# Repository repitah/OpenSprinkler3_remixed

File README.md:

# OpenSprinkler3_remixed
Custom board based off OpenSprinkler 3 using ESP12 ESP8266 board.
The mainboard is split from the driver board allowing a separation of parts and was cheaper for me to implement a smaller system. 

Design uses EagleCAD

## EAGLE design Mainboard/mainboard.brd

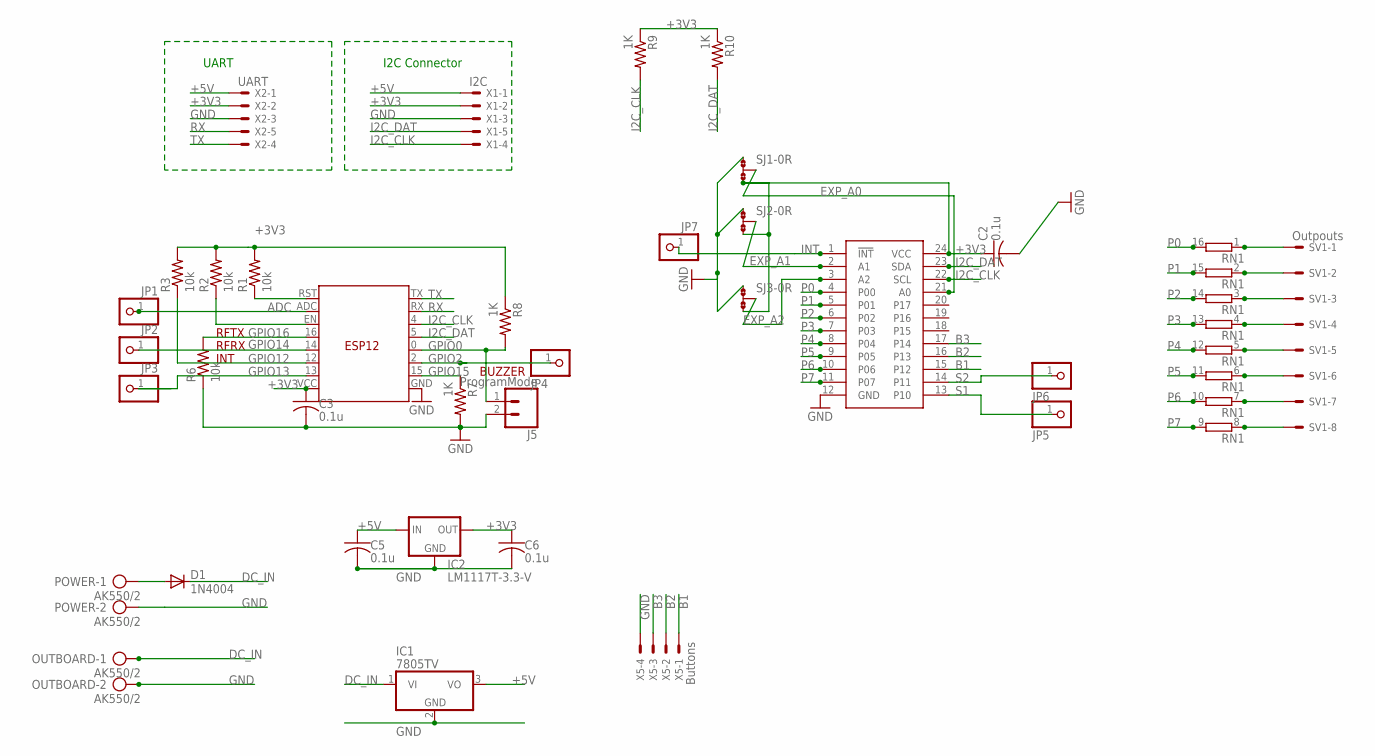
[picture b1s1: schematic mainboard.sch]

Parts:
C2, C3, C5, C6: 0.1u; C050-045X075
D1: 1N4004; DO41-10
ESP: ESP-12N; ESP12_WES
IC1: 7805TV; TO220V
IC2: LM1117T-3.3-V; TO220V
J5: ProgramMode; 1X02
JP1, JP2, JP3, JP4, JP5, JP6, JP7: PINHD-1X1; 1X01
OUTBOARD: AK550/2
PCA9555: PCA9555; TSSOP24
POWER: AK550/2
R1, R3, R6: 10k; 0204/7
R2: 10k; 0204/5
R7, R8, R9, R10: 1K; 0204/7
RN1: 8R-P; DIL16
SJ1, SJ2, SJ3: 0R-JUMPA; A0R-JMP
SV1: Outpouts; 22-23-2081
X1: I2C; 22-23-2051
X2: UART; 22-23-2051
X5: Buttons; 22-23-2041

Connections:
+3V3: C2.1, C3.1, C6.1, ESP.VCC, IC2.2 (OUT), PCA9555.24 (VCC), R1.2, R2.2, R3.2, R8.1, R9.1, R10.1, SJ1.3, SJ2.3, SJ3.3, X1.2, X2.2
+5V: C5.1, IC1.3 (VO), IC2.3 (IN), X1.1, X2.1
ADC: ESP.ADC, JP1.1
B1: PCA9555.15 (P12), X5.1
B2: PCA9555.16 (P13), X5.2
B3: PCA9555.17 (P14), X5.3
DC_IN: D1.C, IC1.1 (VI), OUTBOARD.1
EXP_A0: PCA9555.21 (A0), SJ1.2
EXP_A1: PCA9555.2 (A1), SJ2.2
EXP_A2: PCA9555.3 (A2), SJ3.2
GND: C2.2, C3.2, C5.2, C6.2, ESP.GND, IC1.2 (GND), IC2.1 (GND), J5.2, OUTBOARD.2, PCA9555.12 (GND), POWER.2, R6.1, R7.2, SJ1.1, SJ2.1, SJ3.1, X1.3, X2.3, X5.4
GPIO0: ESP.0 (G0), J5.1, R8.2
GPIO2: ESP.2 (G2), JP4.1
GPIO12: ESP.12 (G12), R3.1
GPIO13: ESP.13 (G13), JP3.1
GPIO14: ESP.14 (G14), JP2.1
GPIO15: ESP.15 (G15), R7.1
GPIO16: ESP.16 (G16), R6.2
I2C_CLK: ESP.4 (G4), PCA9555.22 (SCL), R9.2, X1.4
I2C_DAT: ESP.5 (G5), PCA9555.23 (SDA), R10.2, X1.5
INT: JP7.1, PCA9555.1 (!INT)
unnamed: D1.A, POWER.1
unnamed: ESP.EN, R2.1
unnamed: RN1.1, SV1.1
unnamed: RN1.2 (1), SV1.2
unnamed: RN1.3 (1), SV1.3
unnamed: RN1.4 (1), SV1.4
unnamed: RN1.5 (1), SV1.5
unnamed: RN1.6 (1), SV1.6
unnamed: RN1.7 (1), SV1.7
unnamed: RN1.8 (1), SV1.8
unnamed: ESP.RST, R1.1
P0: PCA9555.4 (P00), RN1.16 (2)
P1: PCA9555.5 (P01), RN1.15 (2)
P2: PCA9555.6 (P02), RN1.14 (2)
P3: PCA9555.7 (P03), RN1.13 (2)
P4: PCA9555.8 (P04), RN1.12 (2)
P5: PCA9555.9 (P05), RN1.11 (2)
P6: PCA9555.10 (P06), RN1.10 (2)
P7: PCA9555.11 (P07), RN1.9 (2)
RX: ESP.RX, X2.5
S1: JP5.1, PCA9555.13 (P10)
S2: JP6.1, PCA9555.14 (P11)
TX: ESP.TX, X2.4

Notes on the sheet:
I2C Connector
UART
RFRX
BUZZER
RFTX
INT

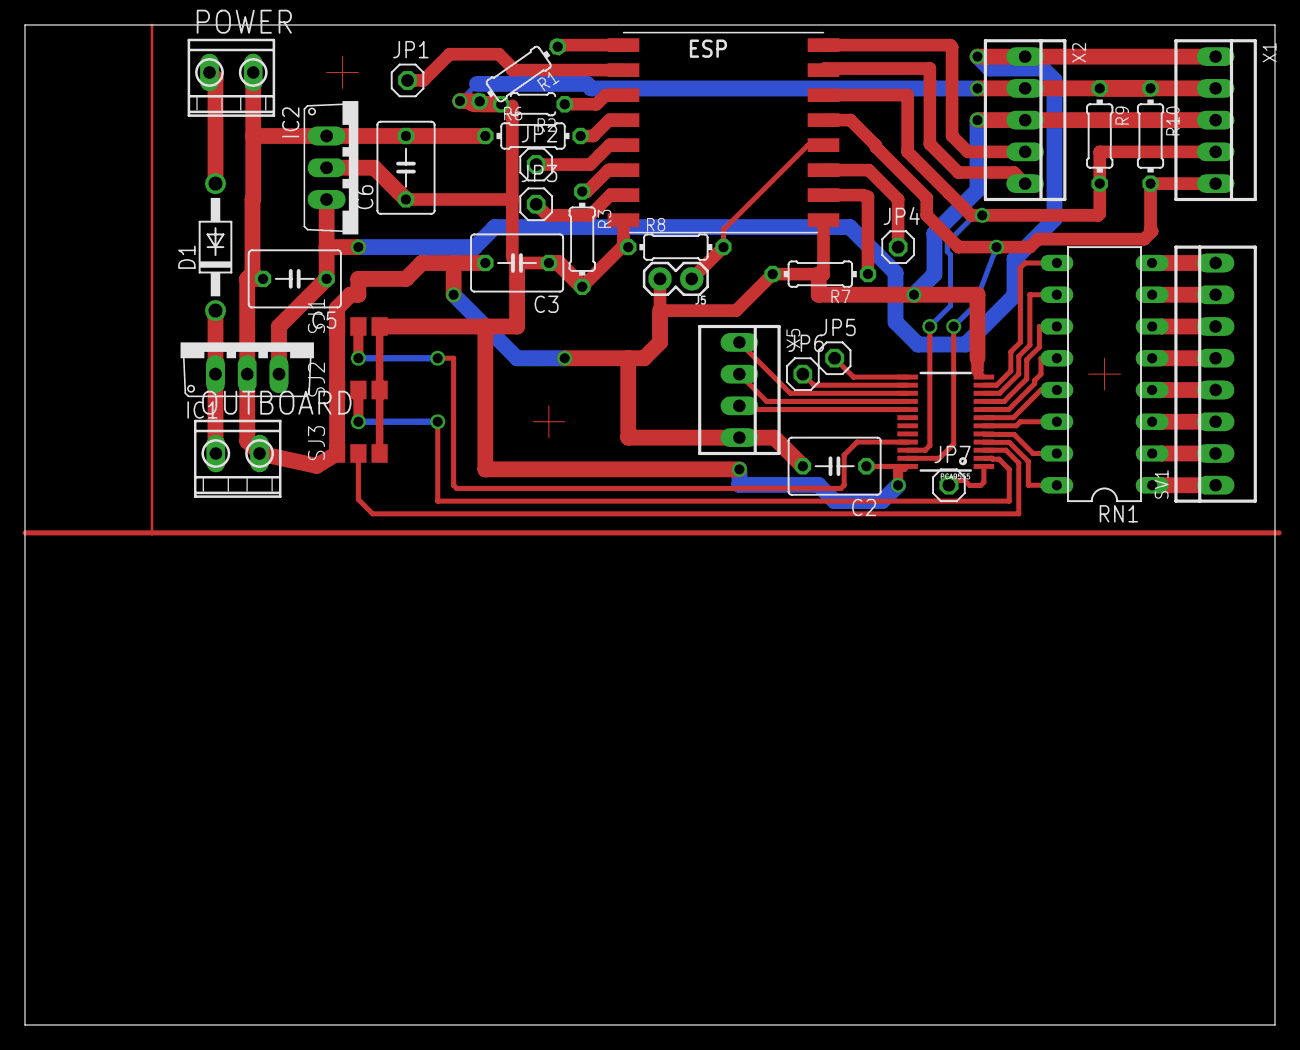
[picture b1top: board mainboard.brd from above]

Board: 2 copper layers, 100.0 x 80.0 mm, 35 parts (0 on the bottom side), 44 nets.

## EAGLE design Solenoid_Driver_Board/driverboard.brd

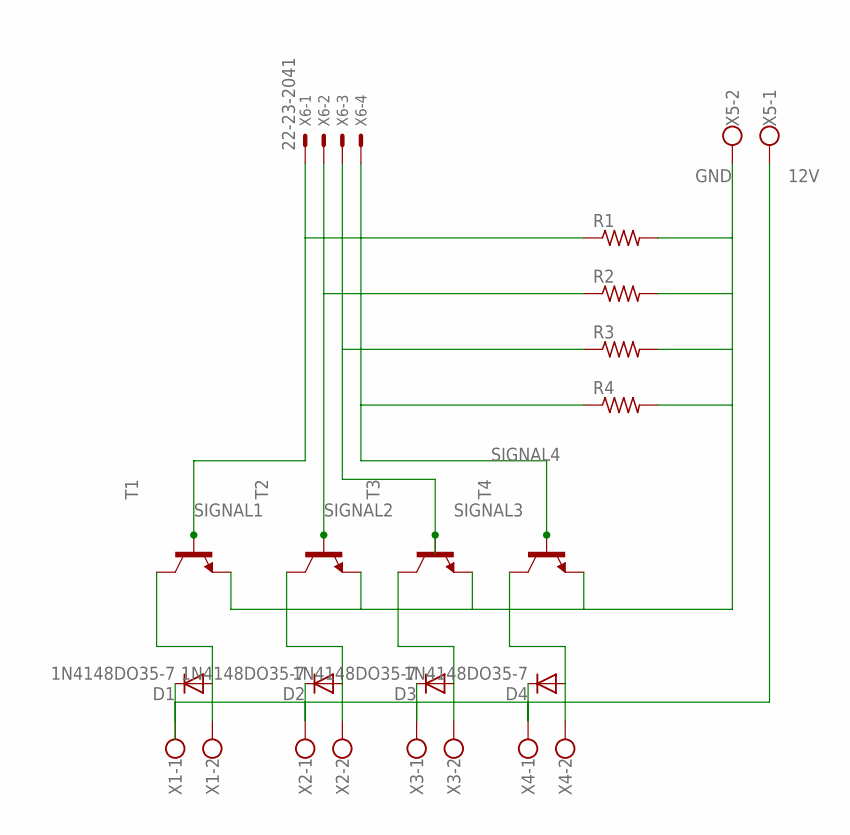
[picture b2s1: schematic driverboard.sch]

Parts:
D1, D2, D3, D4: 1N4148DO35-7; DO35-7
R1, R2, R3, R4: R-US_0204/7; 0204/7
T1, T2, T3, T4: BCV72-NPN-SOT23-BEC; SOT23-BEC
X1, X2, X3, X4, X5: W237-102
X6: 22-23-2041

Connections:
12V: D1.C, D2.C, D3.C, D4.C, X1.1, X2.1, X3.1, X4.1, X5.1
GND: R1.2, R2.2, R3.2, R4.2, T1.E, T2.E, T3.E, T4.E, X5.2
unnamed: D4.A, T4.C, X4.2
unnamed: D3.A, T3.C, X3.2
unnamed: D2.A, T2.C, X2.2
unnamed: D1.A, T1.C, X1.2
SIGNAL1: R1.1, T1.B, X6.1
SIGNAL2: R2.1, T2.B, X6.2
SIGNAL3: R3.1, T3.B, X6.3
SIGNAL4: R4.1, T4.B, X6.4

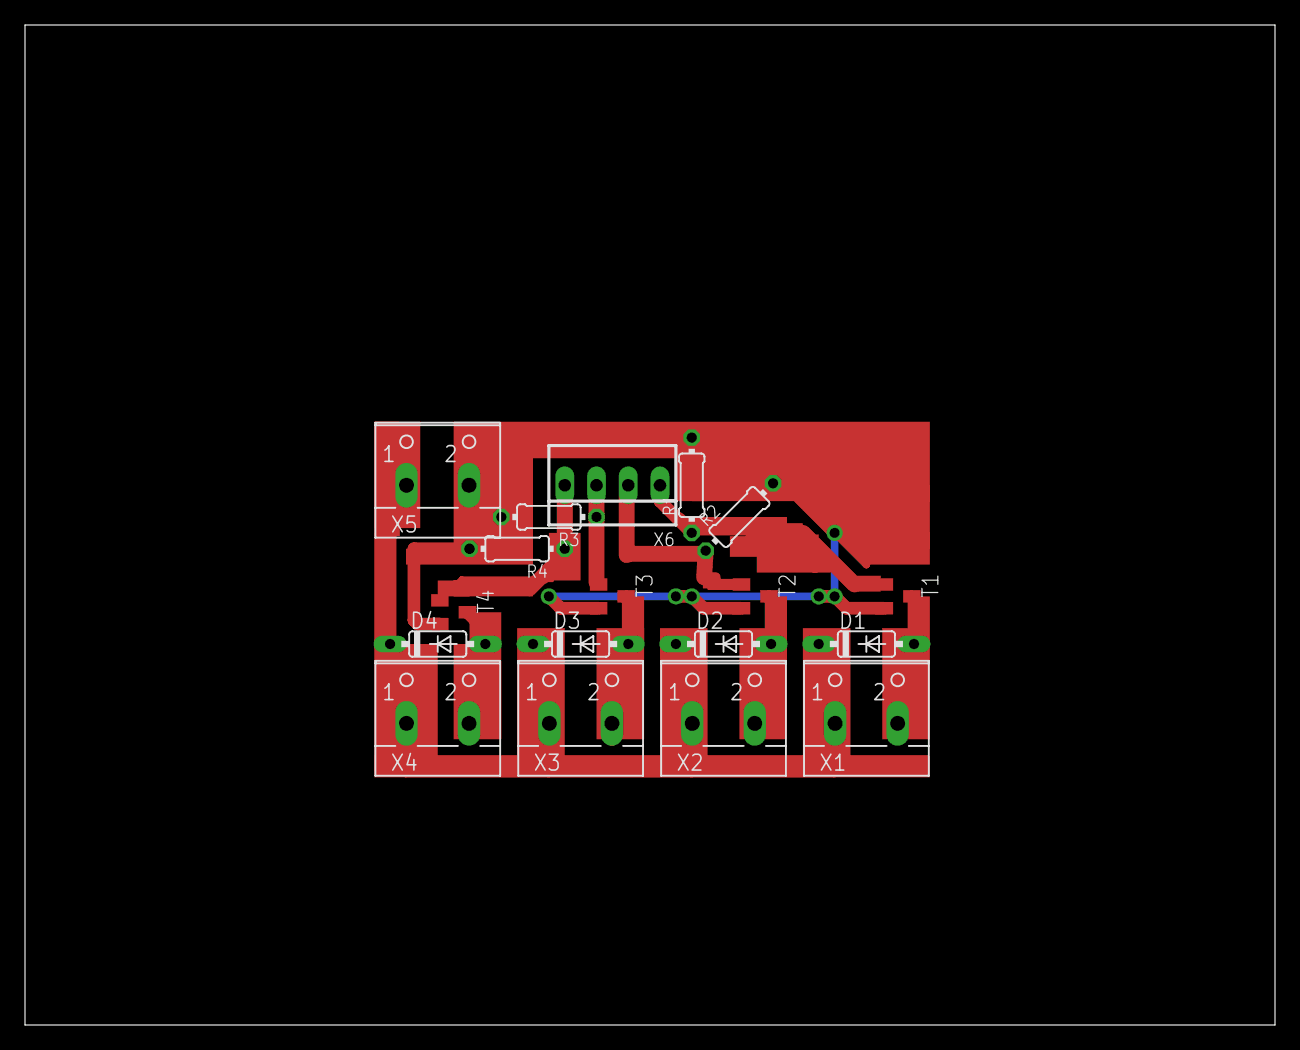
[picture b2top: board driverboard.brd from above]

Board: 2 copper layers, 100.0 x 80.0 mm, 18 parts (0 on the bottom side), 10 nets.

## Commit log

2024-06-30 Add files via upload
    Initial file dump from completed project

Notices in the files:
parts and their libraries:
SparkFun-Connectors: Licensing: Creative Commons ShareAlike 4.0 International - https://creativecommons.org/licenses/by-sa/4.0
SparkFunNew: Licensing: CC v3.0 Share-Alike You are welcome to use this library for commercial purposes.
